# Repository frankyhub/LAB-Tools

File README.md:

<div align="center">

|[:skull:ISSUE](https://github.com/frankyhub/LAB-Tools/issues?q=is%3Aissue)|[:speech_balloon: Forum /Discussion](https://github.com/frankyhub/LAB-Tools/discussions)|[:grey_question:WiKi](https://github.com/frankyhub/LAB-Tools/wiki)||
|--|--|--|--|
| | | | |
<a href="https://github.com/frankyhub/LAB-Tools/issues">|<a href="https://github.com/frankyhub/LAB-Tools/discussions">|<a href="https://github.com/frankyhub/LAB-Tools/6eleases">||
|| <a href="https://github.com/frankyhub/LAB-Tools/pulse" alt="Activity">| <a href="https://github.com/frankyhub/LAB-Tools/graphs/traffic">  |<a href="https://github.com/frankyhub?tab=stars"> ||

<br> <br>

<br> <br>

<br> <br>

---

<div style="position:absolute; left:2cm; ">   
<ol class="breadcrumb" style="border-top: 2px solid black;border-bottom:2px solid black; height: 45px; width: 900px;"> <p align="center"><a href="#oben">nach oben</a></p></ol>
</div>  

---

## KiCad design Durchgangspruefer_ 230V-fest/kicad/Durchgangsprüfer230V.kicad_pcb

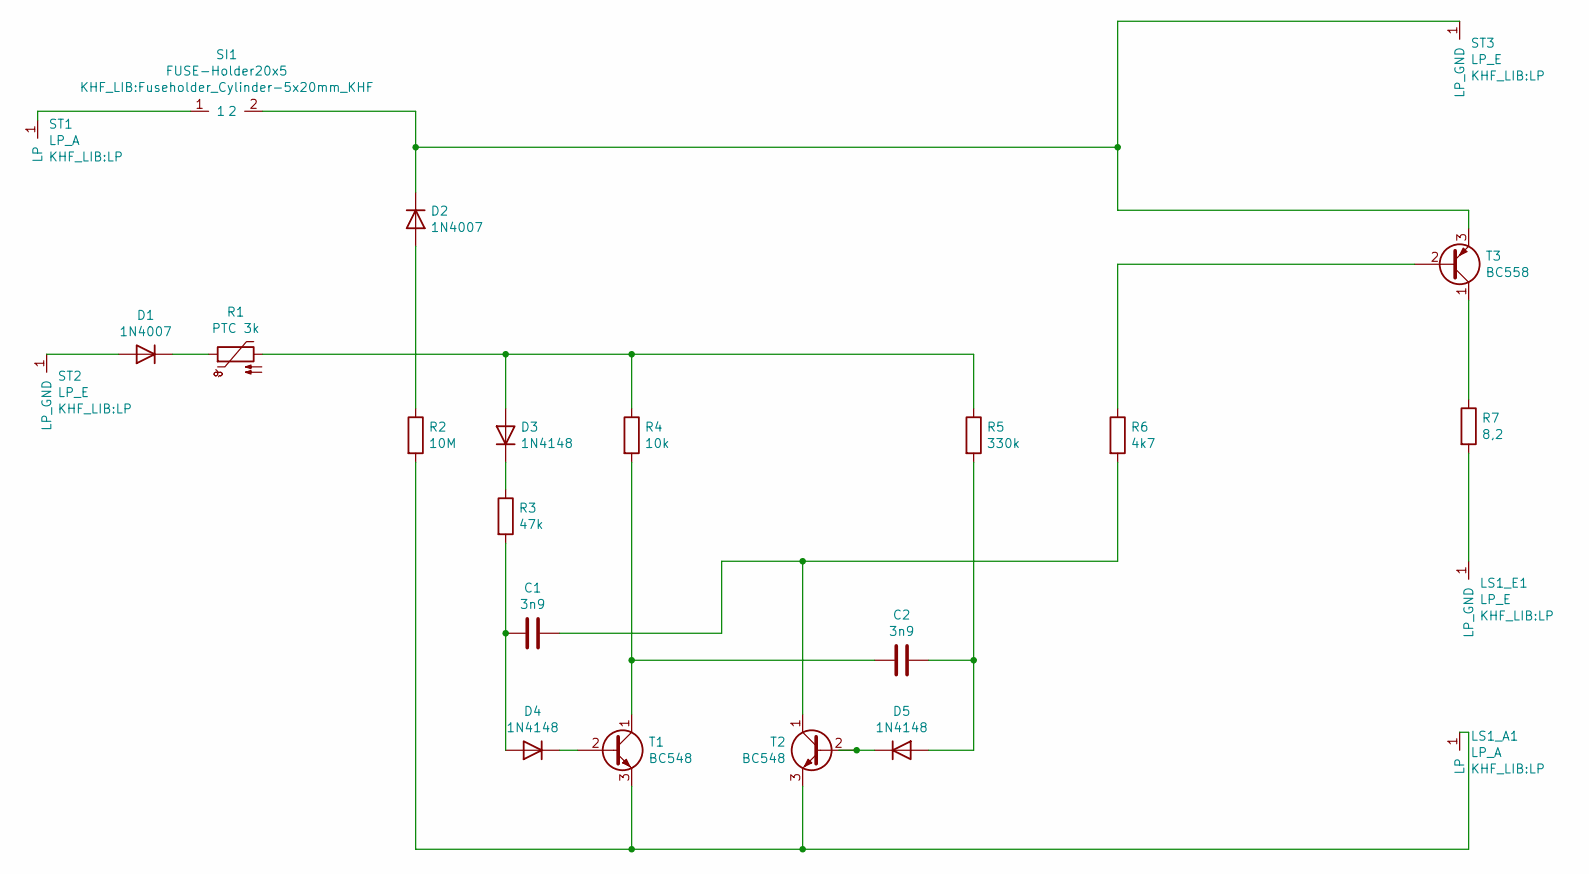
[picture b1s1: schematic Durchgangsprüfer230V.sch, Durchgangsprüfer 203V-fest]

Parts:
C1, C2: 3n9; C_Axial_L5.1mm_D3.1mm_P7.50mm_Horizontal
D1, D2: 1N4007; D_DO-41_SOD81_P10.16mm_Horizontal
D3, D4, D5: 1N4148; D_DO-35_SOD27_P7.62mm_Horizontal
LS1_A1: LP_A; LP
LS1_E1: LP_E; LP
R1: PTC 3k; R_Axial_DIN0204_L3.6mm_D1.6mm_P7.62mm_Horizontal
R2: 10M; R_Axial_DIN0204_L3.6mm_D1.6mm_P7.62mm_Horizontal
R3: 47k; R_Axial_DIN0204_L3.6mm_D1.6mm_P7.62mm_Horizontal
R4: 10k; R_Axial_DIN0204_L3.6mm_D1.6mm_P7.62mm_Horizontal
R5: 330k; R_Axial_DIN0204_L3.6mm_D1.6mm_P7.62mm_Horizontal
R6: 4k7; R_Axial_DIN0204_L3.6mm_D1.6mm_P7.62mm_Horizontal
R7: 8,2; R_Axial_DIN0204_L3.6mm_D1.6mm_P7.62mm_Horizontal
SI1: FUSE-Holder20x5; Fuseholder_Cylinder-5x20mm_KHF
ST1: LP_A; LP
ST2, ST3: LP_E; LP
T1, T2: BC548; TO-92_Inline
T3: BC558; TO-92_Inline

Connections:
unnamed: C1.1, R6.2, T2.1 (C)
unnamed: C1.2, D4.2 (A), R3.2
unnamed: C2.1, D5.2 (A), R5.2
unnamed: C2.2, R4.2, T1.1 (C)
unnamed: D1.1 (K), R1.1
unnamed: D1.2 (A), ST2.1
unnamed: D2.1 (K), SI1.2, ST3.1, T3.3 (E)
unnamed: D2.2 (A), R2.1
unnamed: D3.1 (K), R3.1
unnamed: D3.2 (A), R1.2, R4.1, R5.1
unnamed: D4.1 (K), T1.2 (B)
unnamed: D5.1 (K), T2.2 (B)
unnamed 12: LS1_A1.1, R2.2, T1.3 (E), T2.3 (E); also elsewhere on the board
unnamed: LS1_E1.1, R7.2
unnamed: R6.1, T3.2 (B)
unnamed: R7.1, T3.1 (C)
unnamed: SI1.1, ST1.1

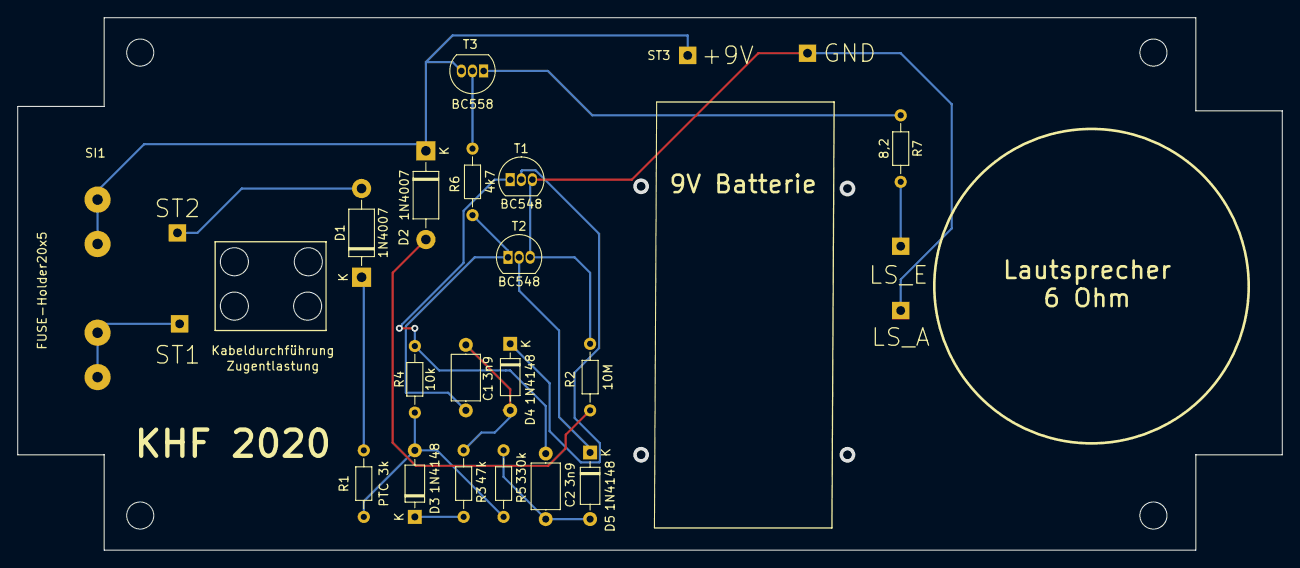
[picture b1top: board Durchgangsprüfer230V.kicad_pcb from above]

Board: 2 copper layers, 144.8 x 61.0 mm, 24 parts (0 on the bottom side), 17 nets.

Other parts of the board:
GND: LP_E; LP

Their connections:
unnamed 12: GND.1; also elsewhere on the board

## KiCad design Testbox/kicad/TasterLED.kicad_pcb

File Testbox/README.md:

# Testbox

## Story
Damit beim Prototypen-Test Wackelkontakte der Jumper auf dem Breadboard vermieden werden, empfielt sich eine Testbox mit 8 LEDs und 8 Taster.

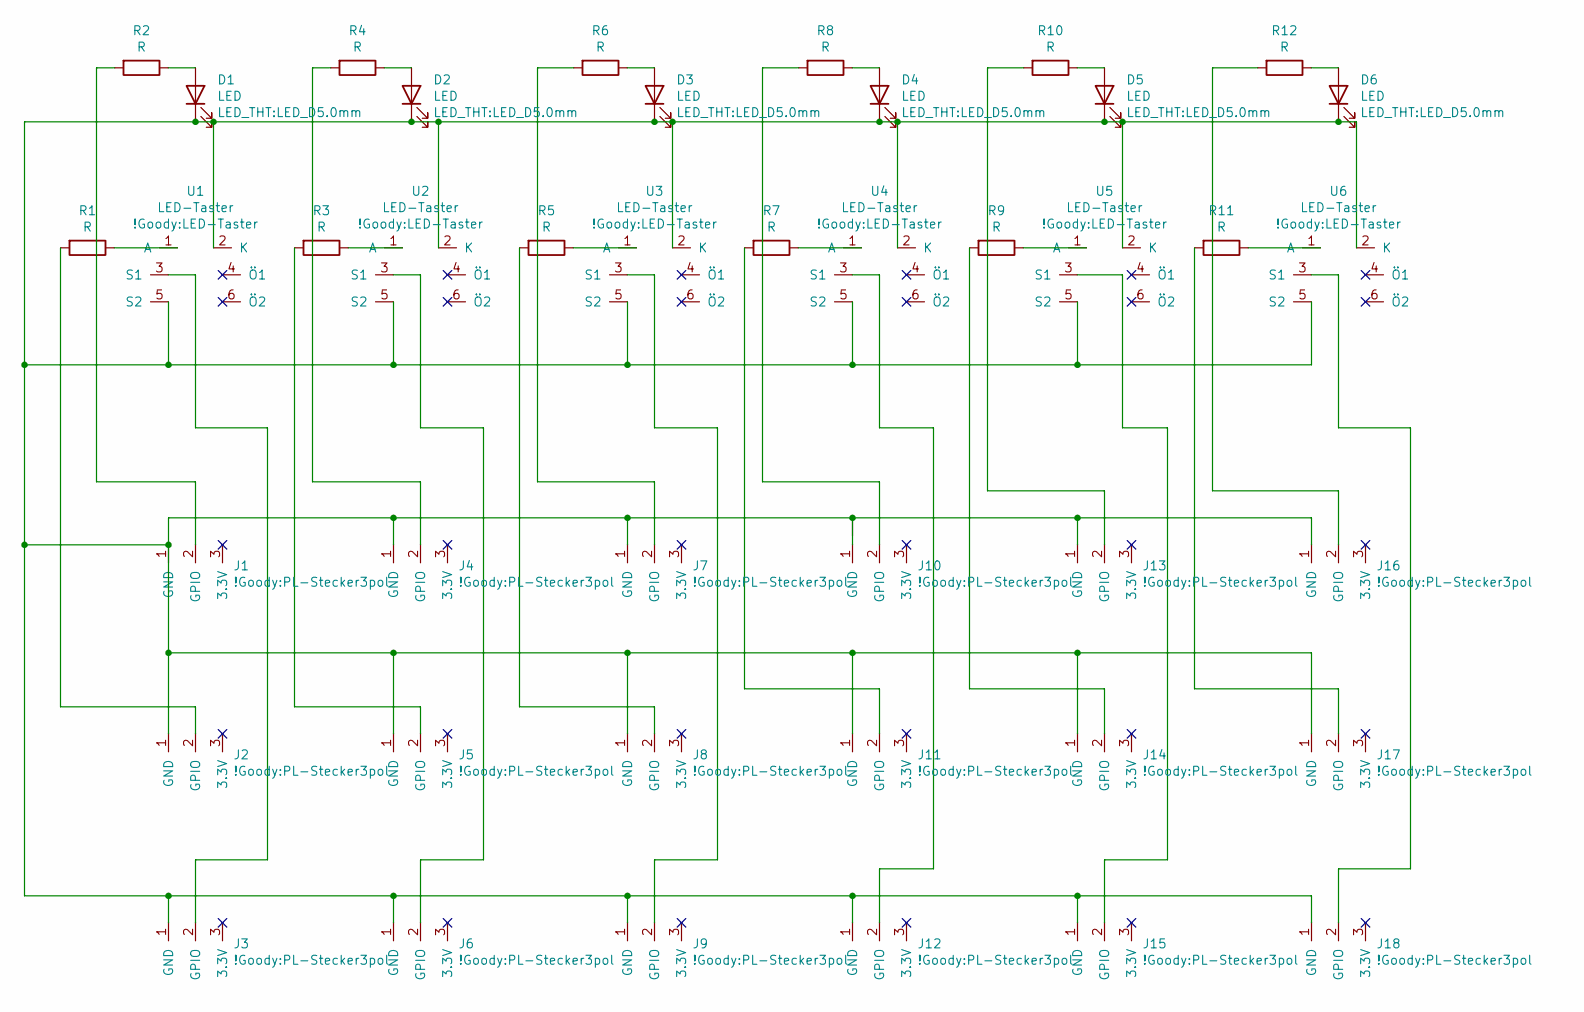
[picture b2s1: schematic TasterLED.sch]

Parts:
D1, D2, D3, D4, D5, D6: LED; LED_D5.0mm
J1, J2, J3, J4, J5, J6, J7, J8, J9, J10, J11, J12, J13, J14, J15, J16, J17, J18: PL-Stecker_3pol; PL-Stecker3pol
R1, R2, R3, R4, R5, R6, R7, R8, R9, R10, R11, R12: R; R_Axial_DIN0309_L9.0mm_D3.2mm_P12.70mm_Horizontal
U1, U2, U3, U4, U5, U6: LED-Taster

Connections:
unnamed: D1.1 (K), D2.1 (K), D3.1 (K), D4.1 (K), D5.1 (K), D6.1 (K), J1.1 (GND), J2.1 (GND), J3.1 (GND), J4.1 (GND), J5.1 (GND), J6.1 (GND), J7.1 (GND), J8.1 (GND), J9.1 (GND), J10.1 (GND), J11.1 (GND), J12.1 (GND), J13.1 (GND), J14.1 (GND), J15.1 (GND), J16.1 (GND), J17.1 (GND), J18.1 (GND), U1.2 (K), U1.5 (S2), U2.2 (K), U2.5 (S2), U3.2 (K), U3.5 (S2), U4.2 (K), U4.5 (S2), U5.2 (K), U5.5 (S2), U6.2 (K), U6.5 (S2)
unnamed: D1.2 (A), R2.1
unnamed: D2.2 (A), R4.1
unnamed: D3.2 (A), R6.1
unnamed: D4.2 (A), R8.1
unnamed: D5.2 (A), R10.1
unnamed: D6.2 (A), R12.1
unnamed: J1.2 (GPIO), R2.2
unnamed: J2.2 (GPIO), R1.2
unnamed: J3.2 (GPIO), U1.3 (S1)
unnamed: J4.2 (GPIO), R4.2
unnamed: J5.2 (GPIO), R3.2
unnamed: J6.2 (GPIO), U2.3 (S1)
unnamed: J7.2 (GPIO), R6.2
unnamed: J8.2 (GPIO), R5.2
unnamed: J9.2 (GPIO), U3.3 (S1)
unnamed: J10.2 (GPIO), R8.2
unnamed: J11.2 (GPIO), R7.2
unnamed: J12.2 (GPIO), U4.3 (S1)
unnamed: J13.2 (GPIO), R10.2
unnamed: J14.2 (GPIO), R9.2
unnamed: J15.2 (GPIO), U5.3 (S1)
unnamed: J16.2 (GPIO), R12.2
unnamed: J17.2 (GPIO), R11.2
unnamed: J18.2 (GPIO), U6.3 (S1)
unnamed: R1.1, U1.1 (A)
unnamed: R3.1, U2.1 (A)
unnamed: R5.1, U3.1 (A)
unnamed: R7.1, U4.1 (A)
unnamed: R9.1, U5.1 (A)
unnamed: R11.1, U6.1 (A)

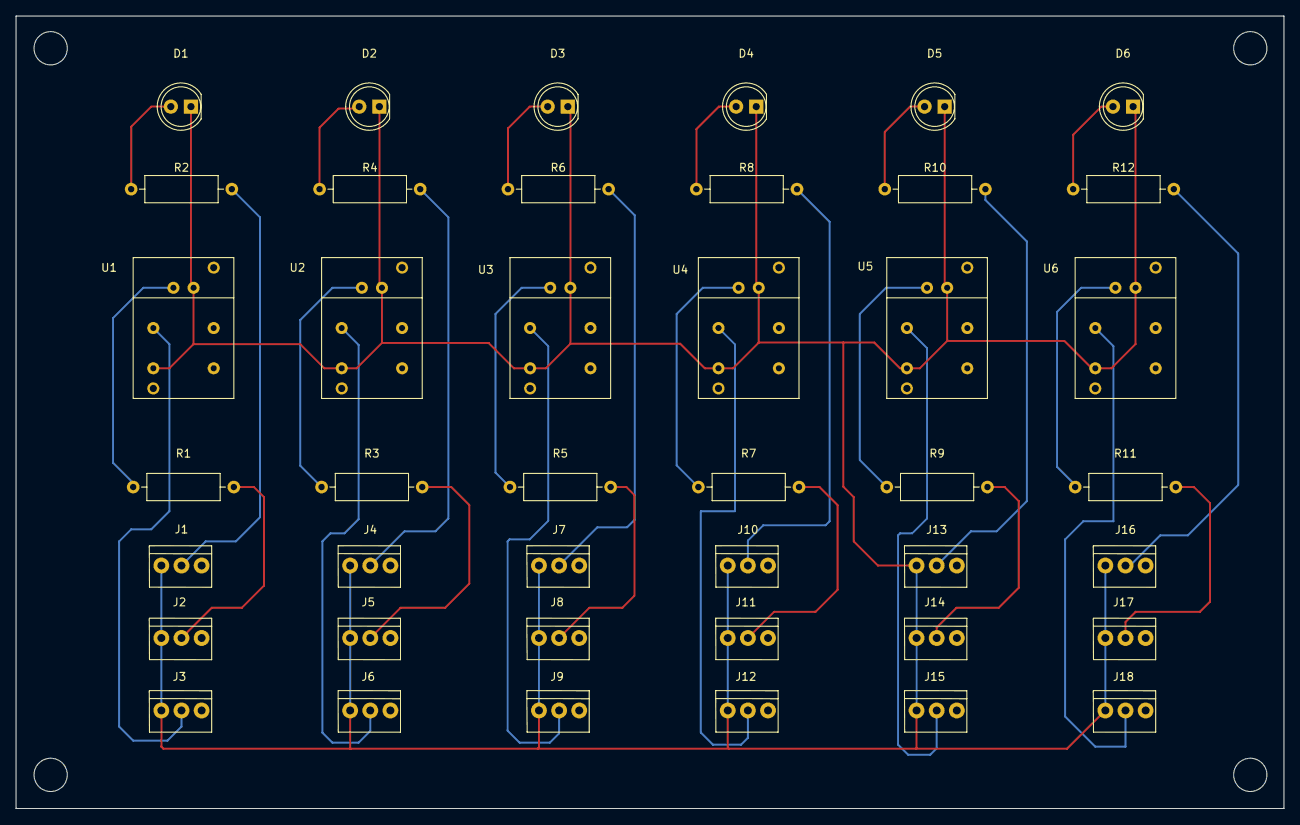
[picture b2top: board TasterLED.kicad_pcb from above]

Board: 2 copper layers, 160.0 x 100.0 mm, 42 parts (0 on the bottom side), 31 nets.

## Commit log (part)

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2024-06-15 V 15.06.2024
2024-06-15 V 15.06.204
2024-07-24 V 24072024
2024-08-23 V 23.08.2024
2024-08-23 V 28.08.2024
2024-09-13 V 13092024
2024-09-25 V 25062024
2024-10-12 V12102024
2024-12-31 Mit Colab erstellt
2024-12-31 V31122024
2026-04-07 V07042026
2026-04-07 V07042026
    Add README with project description and image.
2026-04-13 V13042026
